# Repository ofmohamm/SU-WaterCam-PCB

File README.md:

# SU WaterCam PCB

This repository contains the KiCad design files for a custom PCB for **SU-WaterCam**, integrating the FLIR Lepton thermal camera, Bosch BNO055 IMU, Multitech mDot LoRa module, and Witty Pi 4 RTC board. 

---

## 🔧 Design Overview

- **Layers**: 2-layer PCB (F.Cu, B.Cu)
- **Components**:
  - FLIR Lepton thermal imaging module
  - Bosch BNO055 9-DOF absolute orientation sensor
  - Multitech mDot LoRa module
  - Witty Pi 4 RTC and power manager
- **Power Domains**:
  - 3.3V and 5V rails with copper fill zones
  - Mounting via Witty Pi 4-compatible headers
- **Interfaces**:
  - FFC cutout for FLIR Lepton
  - I²C / UART routing for sensors
  - LoRa antenna trace or u.FL footprint

---

## Electrical & Layout Highlights

- **Trace widths**:
  - Signal: 0.25 mm
  - Power: 0.5 mm (5V rail)
- **Clearance**: 0.20 mm (net class default)
- **Mechanical**:
  - Slot for ribbon cable (Edge.Cuts layer)
  - Mounting holes aligned for case/enclosure compatibility

---

## Custom Libraries

The project uses custom symbols and footprints located in:

- `symbols/mDOT.kicad_sym`
- `footprints/FLIR Lepton.pretty`
- `footprints/MDOT.pretty`
- `footprints/Witty Pi 4.pretty`

Library tables (`fp-lib-table` and `sym-lib-table`) are included and use relative paths for portability.

---

## 📷 PCB Images

- **Wiring/Layout Diagram**  

- **PCB Render**

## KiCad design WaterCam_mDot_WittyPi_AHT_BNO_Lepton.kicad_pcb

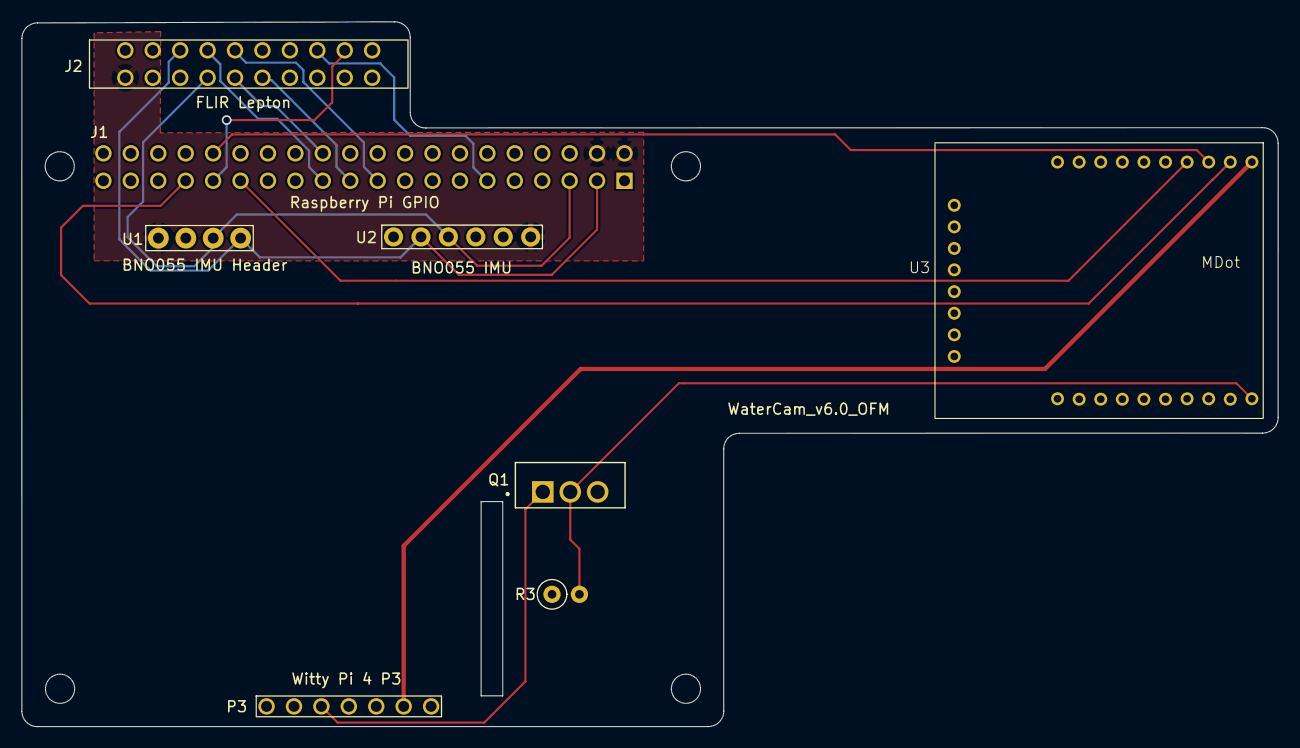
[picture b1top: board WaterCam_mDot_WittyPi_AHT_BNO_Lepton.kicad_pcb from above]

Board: 2 copper layers, 116.3 x 65.3 mm, 8 parts (1 on the bottom side), 16 nets.

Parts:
J1: GPIO; MODULE_RASPBERRY_PI_4B_4GB
J2: FLIR Lepton; FLIR Lepton Breakout Board (Vertical)
P3: Witty Pi 4 P3; WittyPi4_Simple
Q1: NMOS; TO254P1067X483X2057-3
R3: 10kΩ Resistor; R_Axial_DIN0207_L6.3mm_D2.5mm_P2.54mm_Vertical
U1: ATH20; AHT20 Breakout Board
U2: BNO055 IMU; BNO-055 Breakout
U3: MDOT; MTDOT

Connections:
+5V: J1.2, J1.4, J2.2, U1.1 (VIN), U2.6 (VIN)
/GPIO2/SDA1: J1.3, J2.5, U1.4 (SDA), U2.2 (SDA)
/GPIO3/SCL1: J1.5, J2.8, U1.3 (SCL), U2.3 (SCL)
/GPIO5: J1.29, U3.4 (PA_6)
/GPIO6: J1.31, J2.17
/GPIO8/SPI0.CE0: J1.24, J2.10
/GPIO9/SPI0.MISO: J1.21, J2.12
/GPIO10/SPI0.MOSI: J1.19, J2.9
/GPIO11/SPI0.SCLK: J1.23, J2.7
/GPIO12/PWM0: J1.32, U3.3 (PA_3)
/GPIO13/PWM1: J1.33, U3.2 (PA_2)
/GPIO17: J1.11, J2.15
GND: J1.6, J1.9, J1.14, J1.20, J1.25, J1.30, J1.34, J1.39, J2.1, P3.7 (GND), Q1.3 (S), R3.1, U1.2 (GND), U2.4 (GND), U3.10 (GND)
unnamed: P3.2 (3V3), U3.1 (VDD)
unnamed: P3.5 (SW), Q1.1 (D)
unnamed: Q1.2 (G), R3.2, U3.19 (PB_1)

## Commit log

2025-03-12 work in progress schematic for Pi HAT connecting Lepton, mDot, BNO055, AHT20, and WittyPi
2025-03-13 Replace power symbols with direct links to pins
2025-03-14 add footprints for some elements
2025-06-10 feat: complete PCB schematic
    Finalize placement and routing of components. Improve labeling for clarity.
2025-07-21 Add initial WaterCam PCB design integrating FLIR Lepton, BNO055, mDot, and Witty Pi 4
    - Added schematic and PCB layout for 2-layer board in KiCad
    - Integrated custom symbols and footprints (FLIR Lepton, mDot, Witty Pi 4)
    - Included FFC slot for AWM 20624 15-pin ribbon cable
    - Routed 5V and GND copper fills with thermal reliefs
    - Verified design rule compliance (DRC clean)
    - Project includes local symbol and footprint tables for portability
2025-07-23 Refine PCB power and ground layout for improved integrity and manufacturability
    - Localized 5V plane to FLIR and IMU region to reduce EMI and isolate power
    - Maintained full-board GND plane on bottom layer for low-impedance return paths
    - Verified through-hole pad connections to both copper layers
    - Removed unnecessary global power fills to prevent noise injection
    - Cleaned up trace routing and ensured adequate spacing from board edges
2025-07-28 Refactor silkscreen, component labels, and routing to align with Raspberry Pi and improve power integrity
